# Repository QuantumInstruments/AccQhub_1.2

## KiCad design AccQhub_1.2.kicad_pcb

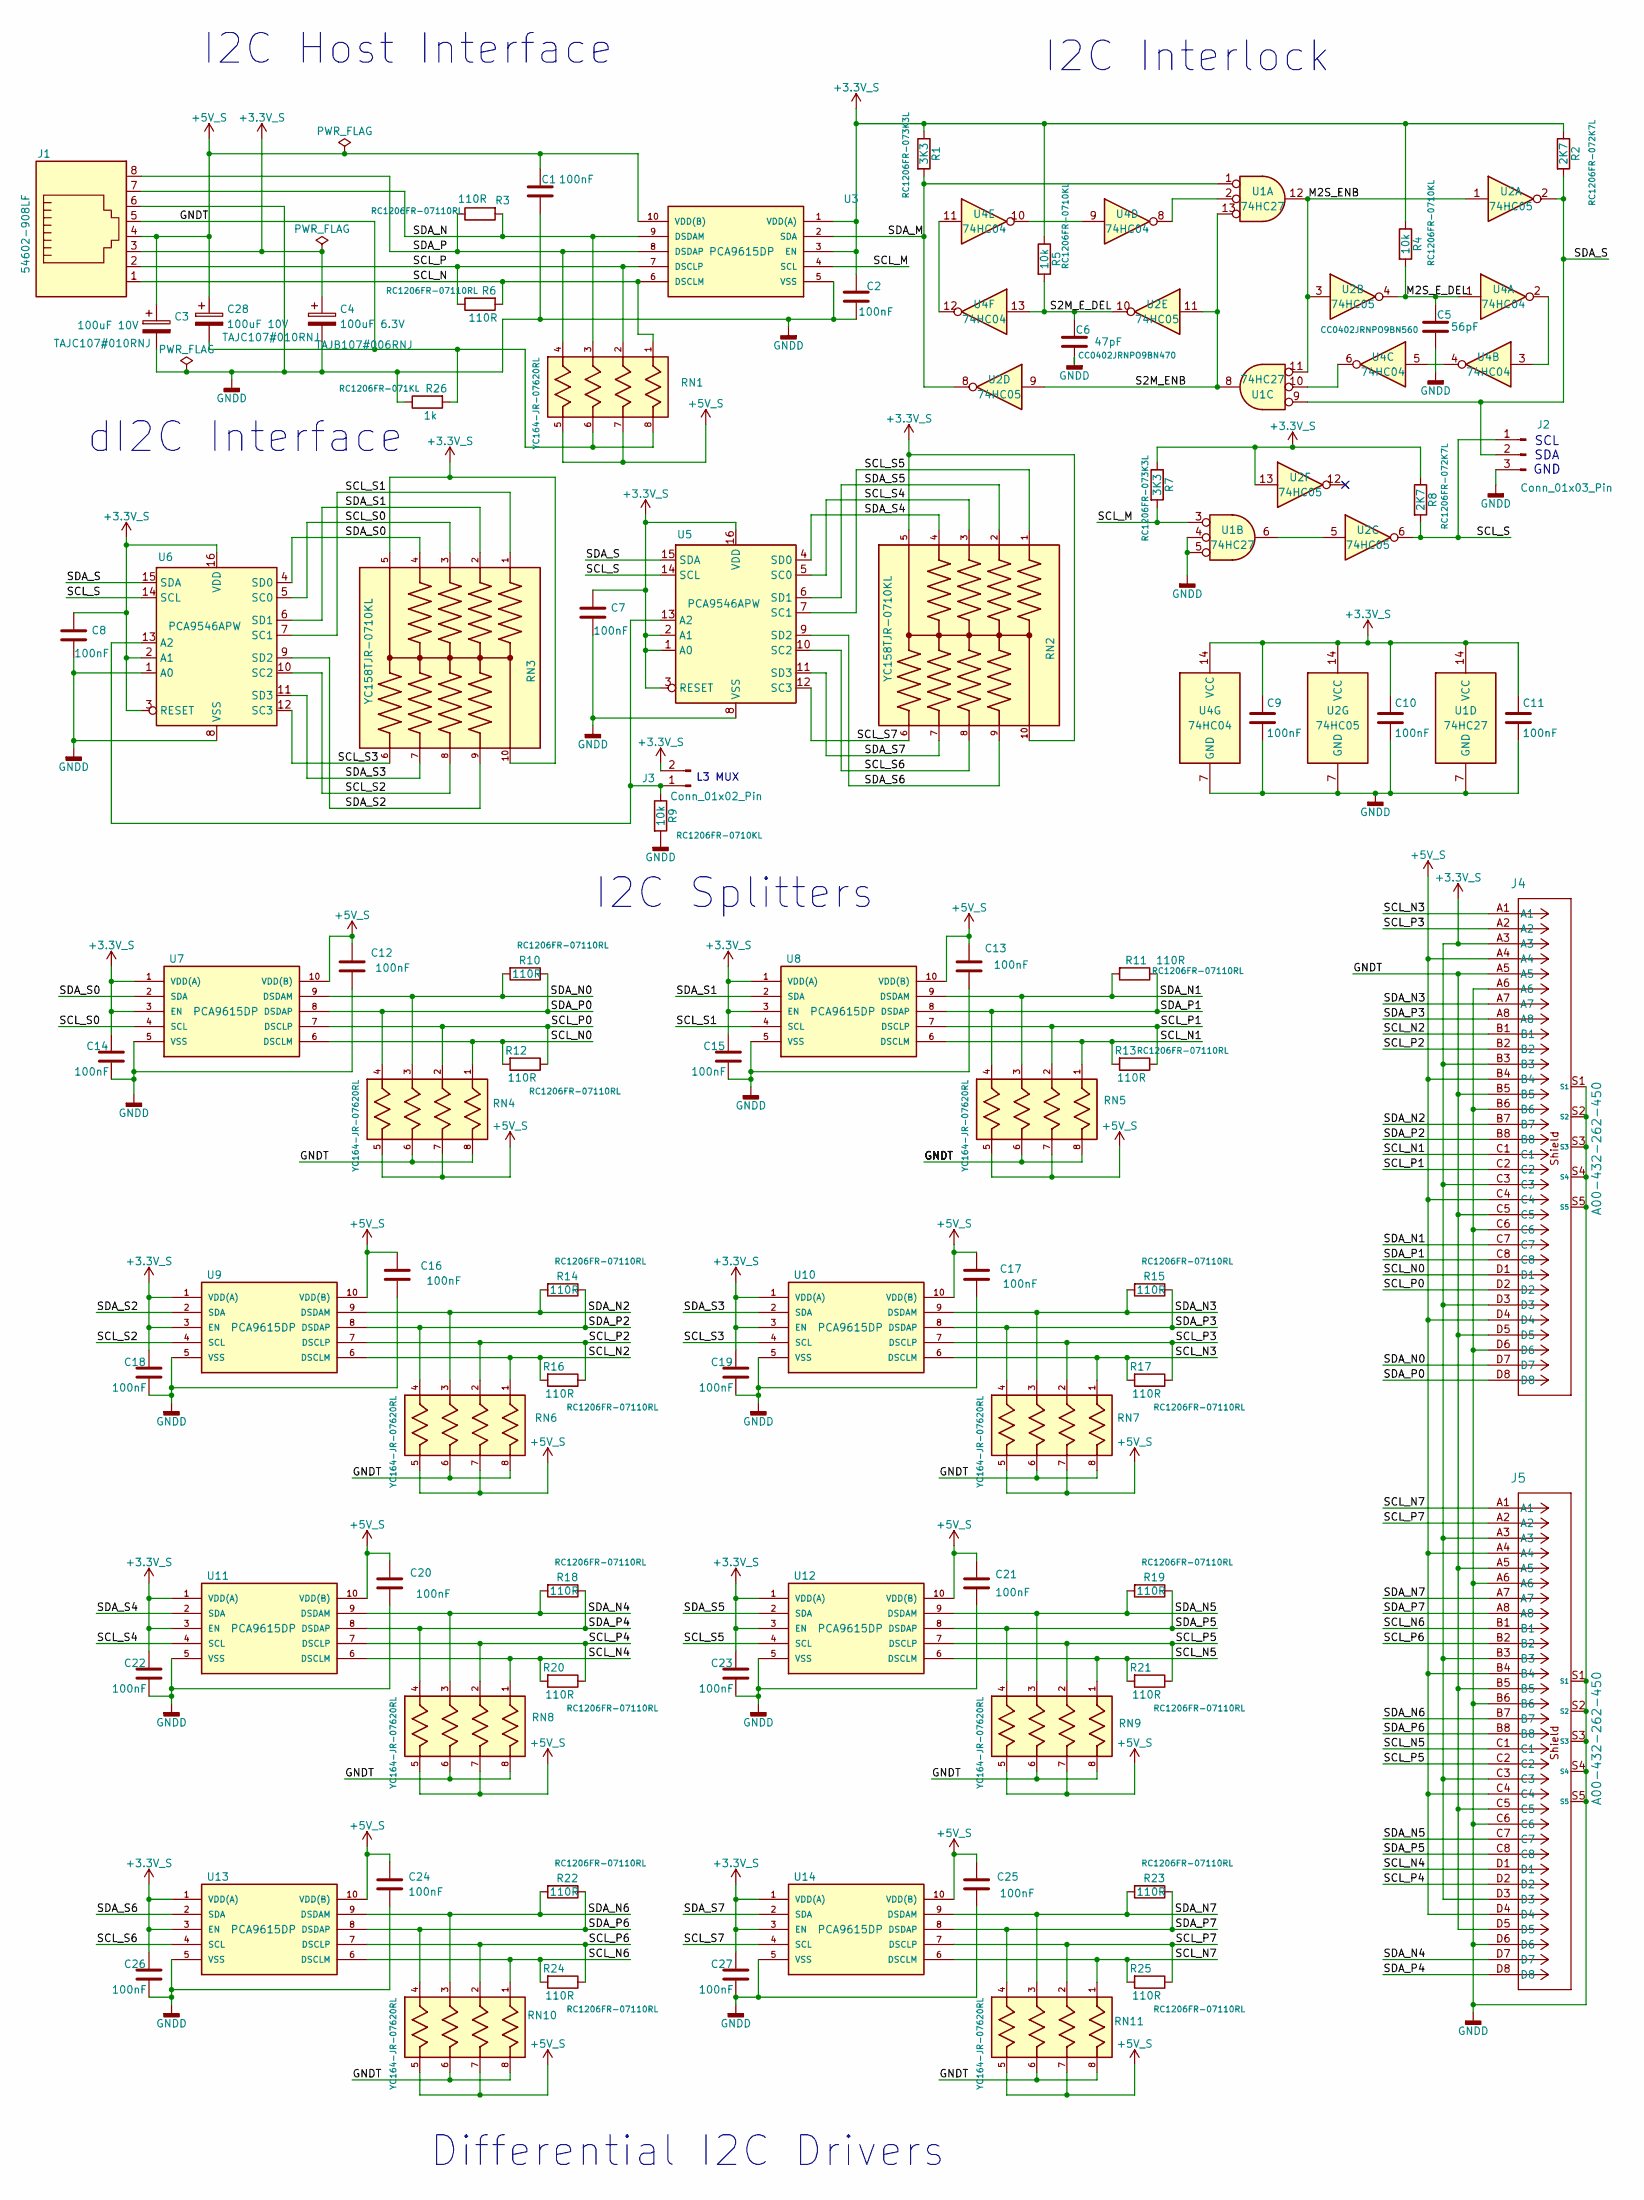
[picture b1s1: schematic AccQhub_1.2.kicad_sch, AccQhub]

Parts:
C1, C2, C7, C8, C9, C10, C11, C12, C13, C14, C15, C16, C17, C18, C19, C20, C21, C22, C23, C24, C25, C26, C27: 100nF; C_0805_2012Metric_Pad1.18x1.45mm_HandSolder
C3, C28: 100uF 10V; CP_EIA-6032-28_Kemet-C_HandSolder; PartNo TAJC107#010RNJ
C4: 100uF 6.3V; CP_EIA-3528-21_Kemet-B_HandSolder; PartNo TAJB107#006RNJ
C5: 56pF; C_0402_1005Metric_Pad0.74x0.62mm_HandSolder; PartNo CC0402JRNPO9BN560
C6: 47pF; C_0402_1005Metric_Pad0.74x0.62mm_HandSolder; PartNo CC0402JRNPO9BN470
J1: 54602-908LF; AMPHENOL_54602-908LF; PartNo 54602-908LF
J2: Conn_01x03_Pin; PinHeader_1x03_P2.54mm_Vertical; PartNo 61300311121
J3: Conn_01x02_Pin; PinHeader_1x02_P2.54mm_Vertical; PartNo 61300211121
J4, J5: A00-432-262-450; CONN_A00-432-262-450_EDA; PartNo A00-432-262-450
R1, R7: 3K3; R_1206_3216Metric_Pad1.30x1.75mm_HandSolder; PartNo RC1206FR-073K3L
R2, R8: 2K7; R_1206_3216Metric_Pad1.30x1.75mm_HandSolder; PartNo RC1206FR-072K7L
R3, R6, R10, R11, R12, R13, R14, R15, R16, R17, R18, R19, R20, R21, R22, R23, R24, R25: 110R; R_1206_3216Metric_Pad1.30x1.75mm_HandSolder; PartNo RC1206FR-07110RL
R4, R5, R9: 10k; R_1206_3216Metric_Pad1.30x1.75mm_HandSolder; PartNo RC1206FR-0710KL
R26: 1k; R_1206_3216Metric_Pad1.30x1.75mm_HandSolder; PartNo RC1206FR-071KL
RN1, RN4, RN5, RN6, RN7, RN8, RN9, RN10, RN11: YC164-JR-07620RL; R_Array_Convex_4x0603; PARTREV 0
RN2: YC158TJR-0710KL; RESCAXE64P320X160X70-10N
RN3: YC158TJR-0710KL; RESCAXE64P320X160X70-10N; PartNo YC158TJR-0710KL
U1: 74HC27; SSOP-14_5.3x6.2mm_P0.65mm; PartNo SN74HC27DBR
U2: 74HC05; TSSOP-14_4.4x5mm_P0.65mm; PartNo SN74HC05PWR
U3, U7, U8, U9, U10, U11, U12, U13, U14: PCA9615DP; TSSOP-10_3x3mm_P0.5mm; PartNo PCA9615DPZ
U4: 74HC04; TSSOP-14_4.4x5mm_P0.65mm; PartNo SN74HC04PWR
U5, U6: PCA9546APW; TSSOP-16_4.4x5mm_P0.65mm; PartNo PCA9546APW

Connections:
+3.3V_S: C2.1, C4.1, C7.1, C8.1, C9.1, C10.1, C11.1, C14.1, C15.1, C18.1, C19.1, C22.1, C23.1, C26.1, C27.1, J1.3, J3.2, J4.A3, J4.B3, J4.C3, J4.D3, J5.A3, J5.B3, J5.C3, J5.D3, R1.1, R2.1, R4.1, R5.1, R7.1, R8.1, RN2.5, RN2.10, RN3.5, RN3.10, U1.14 (VCC), U2.13, U2.14 (VCC), U3.1 (VDD(A)), U3.3 (EN), U4.14 (VCC), U5.1 (A0), U5.2 (A1), U5.3 (RESET), U5.16 (VDD), U6.2 (A1), U6.3 (RESET), U6.16 (VDD), U7.1 (VDD(A)), U7.3 (EN), U8.1 (VDD(A)), U8.3 (EN), U9.1 (VDD(A)), U9.3 (EN), U10.1 (VDD(A)), U10.3 (EN), U11.1 (VDD(A)), U11.3 (EN), U12.1 (VDD(A)), U12.3 (EN), U13.1 (VDD(A)), U13.3 (EN), U14.1 (VDD(A)), U14.3 (EN)
+5V_S: C1.1, C3.1, C12.1, C13.1, C16.1, C17.1, C20.1, C21.1, C24.1, C25.1, C28.1, J1.4, J4.A4, J4.B4, J4.C4, J4.D4, J5.A4, J5.B4, J5.C4, J5.D4, RN1.5, RN1.7, RN4.5, RN4.7, RN5.5, RN5.7, RN6.5, RN6.7, RN7.5, RN7.7, RN8.5, RN8.7, RN9.5, RN9.7, RN10.5, RN10.7, RN11.5, RN11.7, U3.10 (VDD(B)), U7.10 (VDD(B)), U8.10 (VDD(B)), U9.10 (VDD(B)), U10.10 (VDD(B)), U11.10 (VDD(B)), U12.10 (VDD(B)), U13.10 (VDD(B)), U14.10 (VDD(B))
/GNDT: C28.2, J1.5, J4.A5, J4.B5, J4.C5, J4.D5, J5.A5, J5.B5, J5.C5, J5.D5, R26.2, RN1.6, RN1.8, RN4.6, RN4.8, RN5.6, RN5.8, RN6.6, RN6.8, RN7.6, RN7.8, RN8.6, RN8.8, RN9.6, RN9.8, RN10.6, RN10.8, RN11.6, RN11.8
/M2S_ENB: U1.11, U1.12, U2.1, U2.3
/M2S_E_DEL: C5.1, R4.2, U2.4, U4.1
/S2M_ENB: U1.8, U1.13, U2.9, U2.11
/S2M_E_DEL: C6.1, R5.2, U2.10, U4.13
/SCL_M: R7.2, U1.3, U3.4 (SCL)
/SCL_N: J1.1, R6.2, RN1.1, U3.6 (DSCLM)
/SCL_N0: J4.D1, R12.2, RN4.1, U7.6 (DSCLM)
/SCL_N1: J4.C1, R13.2, RN5.1, U8.6 (DSCLM)
/SCL_N2: J4.B1, R16.2, RN6.1, U9.6 (DSCLM)
/SCL_N3: J4.A1, R17.2, RN7.1, U10.6 (DSCLM)
/SCL_N4: J5.D1, R20.2, RN8.1, U11.6 (DSCLM)
/SCL_N5: J5.C1, R21.2, RN9.1, U12.6 (DSCLM)
/SCL_N6: J5.B1, R24.2, RN10.1, U13.6 (DSCLM)
/SCL_N7: J5.A1, R25.2, RN11.1, U14.6 (DSCLM)
/SCL_P: J1.2, R6.1, RN1.2, U3.7 (DSCLP)
/SCL_P0: J4.D2, R12.1, RN4.2, U7.7 (DSCLP)
/SCL_P1: J4.C2, R13.1, RN5.2, U8.7 (DSCLP)
/SCL_P2: J4.B2, R16.1, RN6.2, U9.7 (DSCLP)
/SCL_P3: J4.A2, R17.1, RN7.2, U10.7 (DSCLP)
/SCL_P4: J5.D2, R20.1, RN8.2, U11.7 (DSCLP)
/SCL_P5: J5.C2, R21.1, RN9.2, U12.7 (DSCLP)
/SCL_P6: J5.B2, R24.1, RN10.2, U13.7 (DSCLP)
/SCL_P7: J5.A2, R25.1, RN11.2, U14.7 (DSCLP)
/SCL_S: J2.1, R8.2, U2.6, U5.14 (SCL), U6.14 (SCL)
/SCL_S0: RN3.3, U6.5 (SC0), U7.4 (SCL)
/SCL_S1: RN3.1, U6.7 (SC1), U8.4 (SCL)
/SCL_S2: RN3.8, U6.10 (SC2), U9.4 (SCL)
/SCL_S3: RN3.6, U6.12 (SC3), U10.4 (SCL)
/SCL_S4: RN2.3, U5.5 (SC0), U11.4 (SCL)
/SCL_S5: RN2.1, U5.7 (SC1), U12.4 (SCL)
/SCL_S6: RN2.8, U5.10 (SC2), U13.4 (SCL)
/SCL_S7: RN2.6, U5.12 (SC3), U14.4 (SCL)
/SDA_M: R1.2, U1.1, U2.8, U3.2 (SDA)
/SDA_N: J1.7, R3.2, RN1.3, U3.9 (DSDAM)
/SDA_N0: J4.D7, R10.2, RN4.3, U7.9 (DSDAM)
/SDA_N1: J4.C7, R11.2, RN5.3, U8.9 (DSDAM)
/SDA_N2: J4.B7, R14.2, RN6.3, U9.9 (DSDAM)
/SDA_N3: J4.A7, R15.2, RN7.3, U10.9 (DSDAM)
/SDA_N4: J5.D7, R18.2, RN8.3, U11.9 (DSDAM)
/SDA_N5: J5.C7, R19.2, RN9.3, U12.9 (DSDAM)
/SDA_N6: J5.B7, R22.2, RN10.3, U13.9 (DSDAM)
/SDA_N7: J5.A7, R23.2, RN11.3, U14.9 (DSDAM)
/SDA_P: J1.8, R3.1, RN1.4, U3.8 (DSDAP)
/SDA_P0: J4.D8, R10.1, RN4.4, U7.8 (DSDAP)
/SDA_P1: J4.C8, R11.1, RN5.4, U8.8 (DSDAP)
/SDA_P2: J4.B8, R14.1, RN6.4, U9.8 (DSDAP)
/SDA_P3: J4.A8, R15.1, RN7.4, U10.8 (DSDAP)
/SDA_P4: J5.D8, R18.1, RN8.4, U11.8 (DSDAP)
/SDA_P5: J5.C8, R19.1, RN9.4, U12.8 (DSDAP)
/SDA_P6: J5.B8, R22.1, RN10.4, U13.8 (DSDAP)
/SDA_P7: J5.A8, R23.1, RN11.4, U14.8 (DSDAP)
/SDA_S: J2.2, R2.2, U1.9, U2.2, U5.15 (SDA), U6.15 (SDA)
/SDA_S0: RN3.4, U6.4 (SD0), U7.2 (SDA)
/SDA_S1: RN3.2, U6.6 (SD1), U8.2 (SDA)
/SDA_S2: RN3.9, U6.9 (SD2), U9.2 (SDA)
/SDA_S3: RN3.7, U6.11 (SD3), U10.2 (SDA)
/SDA_S4: RN2.4, U5.4 (SD0), U11.2 (SDA)
/SDA_S5: RN2.2, U5.6 (SD1), U12.2 (SDA)
/SDA_S6: RN2.9, U5.9 (SD2), U13.2 (SDA)
/SDA_S7: RN2.7, U5.11 (SD3), U14.2 (SDA)
GNDD: C1.2, C2.2, C3.2, C4.2, C5.2, C6.2, C7.2, C8.2, C9.2, C10.2, C11.2, C12.2, C13.2, C14.2, C15.2, C16.2, C17.2, C18.2, C19.2, C20.2, C21.2, C22.2, C23.2, C24.2, C25.2, C26.2, C27.2, J1.6, J2.3, J4.A6, J4.B6, J4.C6, J4.D6, J4.S1, J4.S2, J4.S3, J4.S4, J4.S5, J5.A6, J5.B6, J5.C6, J5.D6, J5.S1, J5.S2, J5.S3, J5.S4, J5.S5, R9.2, R26.1, U1.4, U1.5, U1.7 (GND), U2.7 (GND), U3.5 (VSS), U4.7 (GND), U5.8 (VSS), U6.1 (A0), U6.8 (VSS), U7.5 (VSS), U8.5 (VSS), U9.5 (VSS), U10.5 (VSS), U11.5 (VSS), U12.5 (VSS), U13.5 (VSS), U14.5 (VSS)
unnamed: J3.1, R9.1, U5.13 (A2), U6.13 (A2)
unnamed: U1.2, U4.8
unnamed: U1.6, U2.5
unnamed: U1.10, U4.6
unnamed: U4.2, U4.3
unnamed: U4.4, U4.5
unnamed: U4.9, U4.10
unnamed: U4.11, U4.12

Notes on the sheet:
I2C Interlock
L3 MUX
I2C Splitters
dI2C Interface
SCL SDA GND
Differential I2C Drivers
I2C Host Interface

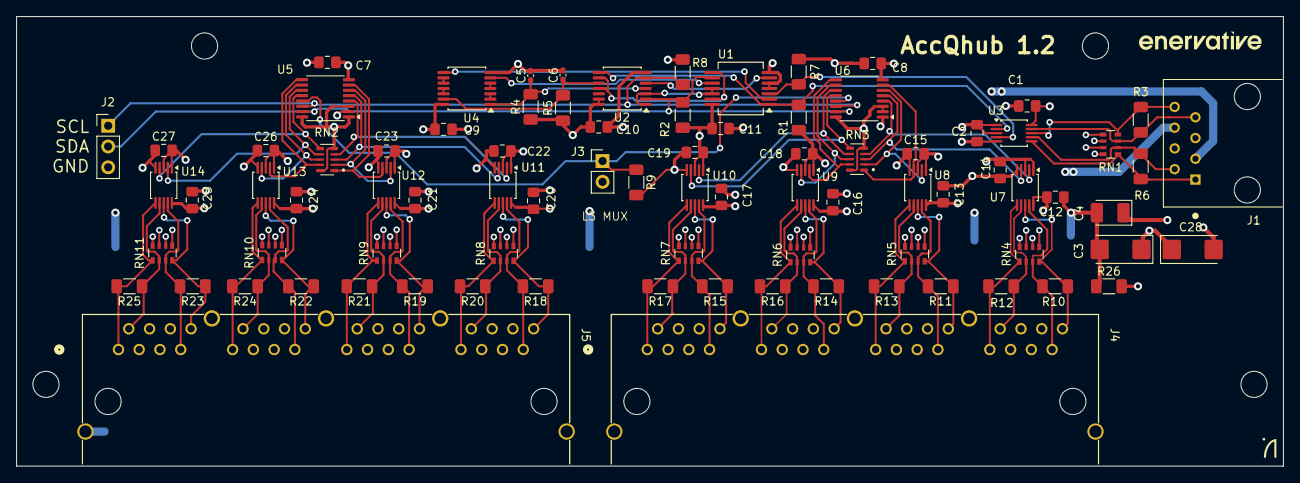
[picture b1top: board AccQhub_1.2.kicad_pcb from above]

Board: 4 copper layers, 155.0 x 55.0 mm, 90 parts (0 on the bottom side), 72 nets.

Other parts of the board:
L: LOGO; Enervative_logo_15
L#2: LOGO; QI_logo2-5
MH1, MH2, MH3, MH4: MountingHole_3.2mm_M3

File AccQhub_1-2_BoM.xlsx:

Enervative AccQ Hub 1.2 BoM - 2026-10-31
Designator | Quantity | Value | Footprint | Mount Type | Description | PartNo | Manufacturer | Comments
C1, C10, C11, C12, C13, C14, C15, C16, C17, C18, C19, C2, C20, C21, C22, C23, C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 | 23 | 100nF | C_0805_2012Metric_Pad1.18x1.45mm_HandSolder | smt | MLCC Ceramic Capacitor | CL21B104KBCNNNC | Samsung | Generic part. Alternative manufacturer OK
C28, C3 | 2 | 100uF 10V | CP_EIA-6032-28_Kemet-C_HandSolder | smt | Tantalum Capacitor | TAJC107#010RNJ | Kyocera AXV | Generic part. Alternative manufacturer OK
C4 | 1 | 100uF 6.3V | CP_EIA-3528-21_Kemet-B_HandSolder | smt | Tantalum Capacitor | TAJB107#006RNJ | Kyocera AXV | Generic part. Alternative manufacturer OK
C5 | 1 | 56pF | C_0402_1005Metric_Pad0.74x0.62mm_HandSolder | smt | MLCC capacitor C0G | CC0402JRNPO9BN560 | Kyocera | Generic part. Alternative manufacturer OK
C6 | 1 | 47pF | C_0402_1005Metric_Pad0.74x0.62mm_HandSolder | smt | MLCC capacitor C0G | CC0402JRNPO9BN470 | Kyocera | Generic part. Alternative manufacturer OK
J1 | 1 | 54602-908LF | AMPHENOL_54602-908LF | tht | RJ45 connector, 8P8C w/o LED & Magnetics | 54602-908LF | Amphenol
J2 | 1 | Conn_01x03_Pin | PinHeader_1x03_P2.54mm_Vertical | tht | Generic connector, single row, 01x03 | 61300311121 | Würth | Generic part. Alternative manufacturer OK
J3 | 1 | Conn_01x02_Pin | PinHeader_1x02_P2.54mm_Vertical | tht | Generic connector, single row, 01x02 | 61300211121 | Würth | Generic part. Alternative manufacturer OK
J4, J5 | 2 | A00-432-262-450 | CONN_A00-432-262-450_EDA | tht | 4 x RJ45 jack tab down | A00-432-262-450 | EDAC
R1, R7 | 2 | 3K3 | R_1206_3216Metric_Pad1.30x1.75mm_HandSolder | smt | Resistor 1% 0.25W | RC1206FR-073K3L | Yageo | Generic part. Alternative manufacturer OK
R10, R11, R12, R13, R14, R15, R16, R17, R18, R19, R20, R21, R22, R23, R24, R25,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 | 18 | 110R | R_1206_3216Metric_Pad1.30x1.75mm_HandSolder | smt | Resistor 1% 0.25W | RC1206FR-07110RL | Yageo | Generic part. Alternative manufacturer OK
R2, R8 | 2 | 2K7 | R_1206_3216Metric_Pad1.30x1.75mm_HandSolder | smt | Resistor 1% 0.25W | RC1206FR-072K7L | Yageo | Generic part. Alternative manufacturer OK
R26 | 1 | 1k | R_1206_3216Metric_Pad1.30x1.75mm_HandSolder | smt | Resistor 1% 0.25W | RC1206FR-071KL | Yageo | Generic part. Alternative manufacturer OK
R4, R5, R9 | 3 | 10k | R_1206_3216Metric_Pad1.30x1.75mm_HandSolder | smt | Resistor 1% 0.25W | RC1206FR-0710KL | Yageo | Generic part. Alternative manufacturer OK
RN1, RN10, RN11, RN4, RN5, RN6, RN7, RN8, RN9 | 9 | YC164-JR-07620RL | R_Array_Convex_4x0603 | smt | ±5% 62.5mW Power Per Element Isolated 4 Resistor Network | YC164-JR-07620RL | Yageo | Generic part. Alternative manufacturer OK
RN2, RN3 | 2 | YC158TJR-0710KL | RESCAXE64P320X160X70-10N | smt | 5% 62.5mW Bussed Resistor Network/Array | YC158TJR-0710KL | Yageo | Generic part. Alternative manufacturer OK
U1 | 1 | 74HC27 | SSOP-14_5.3x6.2mm_P0.65mm | smt | Triple 3-input NOR | SN74HC27DBR | Texas
U10, U11, U12, U13, U14, U3, U7, U8, U9 | 9 | PCA9615DP | TSSOP-10_3x3mm_P0.5mm | smt | Buffer, ReDriver 2 Channel 400kHz 10-TSSOP | PCA9615DPZ | NXP
U2 | 1 | 74HC05 | TSSOP-14_4.4x5mm_P0.65mm | smt | Hex Inverter Open Drain | SN74HC05PWR | Texas
U4 | 1 | 74HC04 | TSSOP-14_4.4x5mm_P0.65mm | smt | Hex Inverter | SN74HC04PWR | Texas
U5, U6 | 2 | PCA9546APW | TSSOP-16_4.4x5mm_P0.65mm | smt | 4-channel I2C-bus multiplexer with reset | PCA9546APWR | Texas
Total Parts | 84 |  | Total number of types | 21
Total SMT | 79 |  | Total SMT types | 17
Total THT | 5 |  | Total THD types | 4
